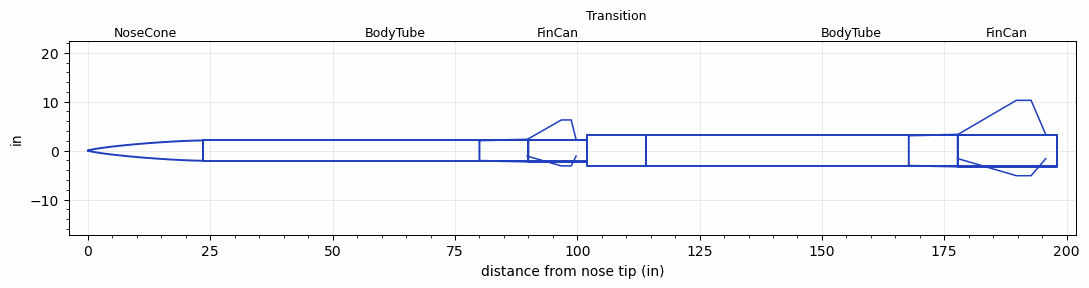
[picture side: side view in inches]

<RASAeroDocument>
 <FileVersion>2</FileVersion>
 <RocketDesign>
  <NoseCone>
   <Length>23.5</Length>
   <Diameter>4.1534</Diameter>
   <Shape>Von Karman Ogive</Shape>
   <Location>0</Location>
  </NoseCone>
  <BodyTube>
   <Length>78.5</Length>
   <Diameter>4.1534</Diameter>
   <Location>23.5</Location>
  </BodyTube>
  <FinCan>
   <Length>12</Length>
   <Diameter>4.5284</Diameter>
   <InsideDiameter>4.1534</InsideDiameter>
   <Location>102</Location>
   <ShoulderLength>10</ShoulderLength>
   <Offset>-12</Offset>
   <Fin>
    <Count>3</Count>
    <Chord>10</Chord>
    <Span>4</Span>
    <SweepDistance>7</SweepDistance>
    <TipChord>2</TipChord>
    <Thickness>0.1875</Thickness>
    <Location>12.25</Location>
    <AirfoilSection>Square</AirfoilSection>
   </Fin>
  </FinCan>
  <Transition>
   <Length>12</Length>
   <Diameter>6.17</Diameter>
   <Location>102</Location>
   <RearDiameter>6.17</RearDiameter>
  </Transition>
  <BodyTube>
   <Length>84</Length>
   <Diameter>6.17</Diameter>
   <Location>114</Location>
  </BodyTube>
  <FinCan>
   <Length>20.25</Length>
   <Diameter>6.545</Diameter>
   <InsideDiameter>6.17</InsideDiameter>
   <Location>198</Location>
   <ShoulderLength>10</ShoulderLength>
   <Offset>-20.25</Offset>
   <Fin>
    <Count>3</Count>
    <Chord>18</Chord>
    <Span>7</Span>
    <SweepDistance>12</SweepDistance>
    <TipChord>3</TipChord>
    <Thickness>0.1875</Thickness>
    <Location>20.25</Location>
    <AirfoilSection>Square</AirfoilSection>
   </Fin>
  </FinCan>
  <Surface>Smooth (Zero Roughness)</Surface>
  <ModifiedBarrowman>False</ModifiedBarrowman>
  <Turbulence>False</Turbulence>
  <UseBooster1>True</UseBooster1>
  <UseBooster2>False</UseBooster2>
 </RocketDesign>
 <LaunchSite>
  <Altitude>3000</Altitude>
  <Pressure>30.3</Pressure>
  <RodAngle>1</RodAngle>
  <RodLength>25</RodLength>
  <Temperature>90</Temperature>
  <WindSpeed>12</WindSpeed>
 </LaunchSite>
 <Recovery>
  <Altitude1>1000</Altitude1>
  <Altitude2>1000</Altitude2>
  <DeviceType1>None</DeviceType1>
  <DeviceType2>None</DeviceType2>
  <Event1>False</Event1>
  <Event2>False</Event2>
  <Size1>1</Size1>
  <Size2>1</Size2>
  <EventType1>None</EventType1>
  <EventType2>None</EventType2>
  <CD1>1.33</CD1>
  <CD2>1.33</CD2>
 </Recovery>
 <SimulationList>
  <Simulation>
   <SustainerLaunchWt>35</SustainerLaunchWt>
   <SustainerNozzleDiameter>2.6</SustainerNozzleDiameter>
   <SustainerCG>57.59</SustainerCG>
   <SustainerIgnitionDelay>0</SustainerIgnitionDelay>
   <Booster1Engine>O3400-IM-P  (CTI)</Booster1Engine>
   <Booster1LaunchWt>150</Booster1LaunchWt>
   <Booster1SeparationDelay>0</Booster1SeparationDelay>
   <Booster1IgnitionDelay>0</Booster1IgnitionDelay>
   <Booster1CG>105</Booster1CG>
   <Booster1NozzleDiameter>5.76</Booster1NozzleDiameter>
   <IncludeBooster1>True</IncludeBooster1>
   <Booster2Delay>0</Booster2Delay>
   <IncludeBooster2>False</IncludeBooster2>
   <TimetoApogee>13.46012</TimetoApogee>
   <MaxAltitude>64206.91</MaxAltitude>
   <MaxVelocity>11443.72</MaxVelocity>
  </Simulation>
 </SimulationList>
</RASAeroDocument>
